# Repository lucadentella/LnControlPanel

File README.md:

# LnControlPanel

## Description

LnControlPanel is an opensource board to create Loconet control panels.

## What's new :tada:

- 23/04/2022, new board version, with MCP23017 chips instead of CJMCU modules
- 05/03/2022, new firmware (2.0) with support for new Adafruit libraries

## Features :trophy:

 - **32** independent channels:
   - each channel can be configured as **input** (to *control*) or as **output** (to *monitor)*
   - each channel can control/monitor a **turnout** or a **sensor**
   - each channel can have its own **address**
 - Two Loconet connectors for **cascade** connection
 - Based on **Arduino** framework and opensource libraries
 - Configurable using a simple **menu** via **serial** connection

## Tutorials :video_camera:
 - [LnControlPanel on Youtube (ENG)](https://youtu.be/r6l4IHOCdZg)
 - [LnControlPanel su Youtube (ITA)](https://youtu.be/eZ9PHgq4dks)

## Resources :open_file_folder:
 - [Eagle files - board with CJMCU modules](https://github.com/lucadentella/LnControlPanel/tree/main/Eagle/Modules) (schematic / PCB)
 - [Eagle files - board with MCP23017 chips](https://github.com/lucadentella/LnControlPanel/tree/main/Eagle/Chips) (schematic / PCB) 
 - [Arduino firmware](https://github.com/lucadentella/LnControlPanel/tree/main/Arduino)

## Documentation :notebook:
 - [Schematic - board with CJMCU modules](https://github.com/lucadentella/LnControlPanel/tree/main/Documentation/Schematics-modules.pdf) (PDF)
 - [Schematic - board with MCP23017 chips](https://github.com/lucadentella/LnControlPanel/tree/main/Documentation/Schematics-chips.pdf) (PDF)
 - [Part list](https://github.com/lucadentella/LnControlPanel/tree/main/Documentation/PARTLIST.md)
 - [How to configure the channels](https://github.com/lucadentella/LnControlPanel/tree/main/Documentation/CONFIGURATION.md)
 - [How to connect buttons/LEDs](https://github.com/lucadentella/LnControlPanel/tree/main/Documentation/CONNECTIONS.md) 

## Requirements :heavy_check_mark:
 - [mrrwa Loconet Library](https://github.com/mrrwa/LocoNet)
 - [Adafruit MCP23017 Library](https://github.com/adafruit/Adafruit-MCP23017-Arduino-Library)

*The libraries above can be installed via the* [Library Manager](https://www.arduino.cc/en/guide/libraries)

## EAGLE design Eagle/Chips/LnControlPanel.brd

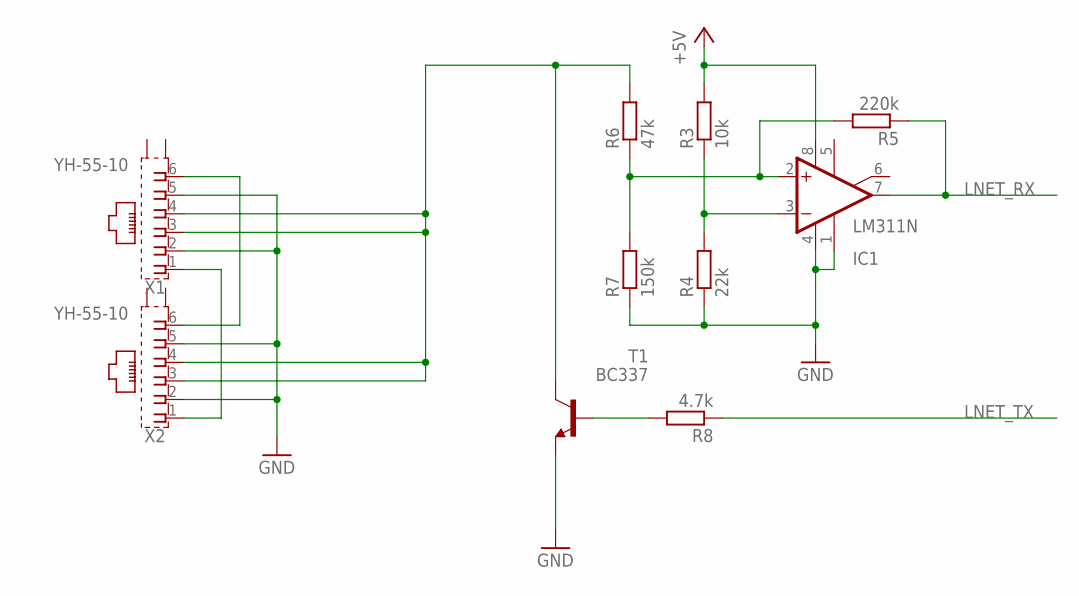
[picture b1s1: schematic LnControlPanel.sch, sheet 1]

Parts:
IC1: LM311N; DIL08
R3: 10k; 0207/2V
R4: 22k; 0207/2V
R5: 220k; 0207/2V
R6: 47k; 0207/2V
R7: 150k; 0207/2V
R8: 4.7k; 0207/2V
T1: BC337; TO92
X1, X2: YH-55-10

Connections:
+5V: IC1.8 (V+), R3.2; also elsewhere on the board
GND: IC1.1 (GND), IC1.4 (V-), R4.1, R7.1, T1.1 (E), X1.2, X1.5, X2.2, X2.5; also elsewhere on the board
LNET: R6.2, T1.3 (C), X1.3, X1.4, X2.3, X2.4
LNET_RX: IC1.7 (OUT), R5.1; also elsewhere on the board
LNET_TX: R8.1; also elsewhere on the board
unnamed: R8.2, T1.2 (B)
unnamed: IC1.3 (-IN), R3.1, R4.2
unnamed: IC1.2 (+IN), R5.2, R6.1, R7.2
unnamed: X1.1, X2.1
unnamed: X1.6, X2.6

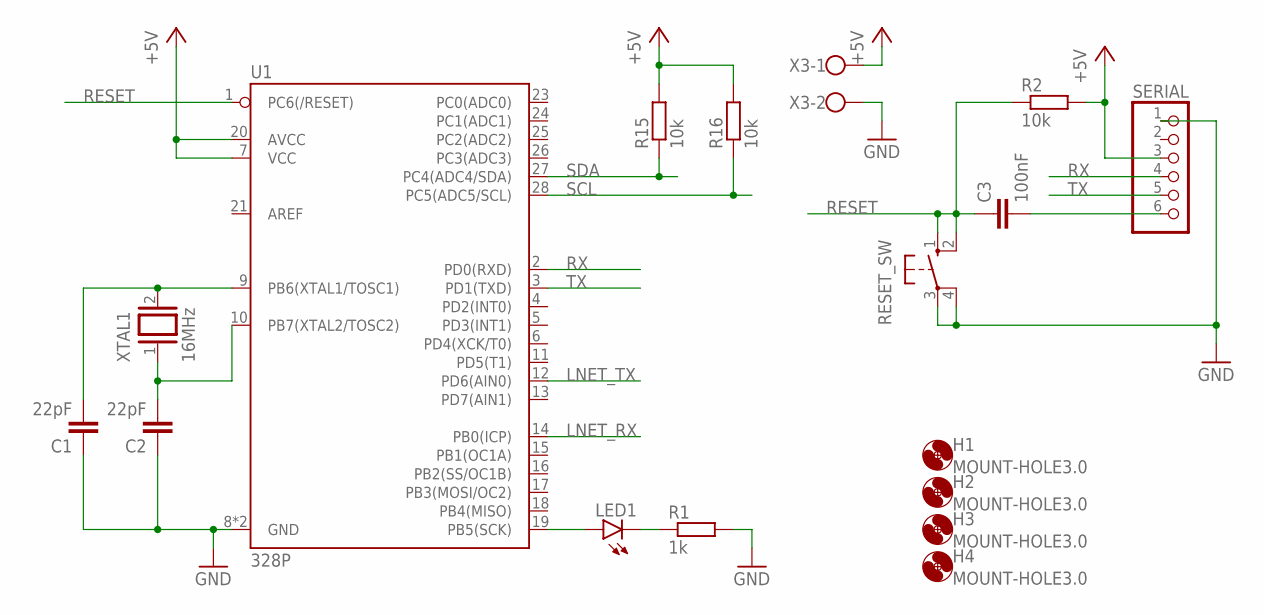
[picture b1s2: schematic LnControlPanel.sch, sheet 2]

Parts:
C1, C2: 22pF; C025-025X050
C3: 100nF; C050-030X075
H1, H2, H3, H4: MOUNT-HOLE3.0; 3,0
LED1: LED3MM
R1: 1k; 0207/2V
R2, R15, R16: 10k; 0207/2V
RESET_SW: 10-XX; B3F-10XX
SERIAL: PINHD-1X6; 1X06
U1: 328P; DIP28
X3: W237-102
XTAL1: 16MHz; QS

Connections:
+5V: R2.2, R15.2, R16.2, SERIAL.3, U1.7 (VCC), U1.20 (AVCC), X3.1; also elsewhere on the board
GND: C1.1, C2.1, R1.2, RESET_SW.3, RESET_SW.4 (P1), SERIAL.1, U1.8 (GND), U1.22 (GND), X3.2; also elsewhere on the board
LNET_RX: U1.14 (PB0(ICP)); also elsewhere on the board
LNET_TX: U1.12 (PD6(AIN0)); also elsewhere on the board
unnamed: C2.2, U1.10 (PB7(XTAL2/TOSC2)), XTAL1.1
unnamed: C1.2, U1.9 (PB6(XTAL1/TOSC1)), XTAL1.2
unnamed: C3.2, SERIAL.6
unnamed: LED1.A, U1.19 (PB5(SCK))
unnamed: LED1.K (C), R1.1
RESET: C3.1, R2.1, RESET_SW.1 (S), RESET_SW.2 (S1), U1.1 (PC6(/RESET))
RX: SERIAL.4, U1.2 (PD0(RXD))
SCL: R16.1, U1.28 (PC5(ADC5/SCL)); also elsewhere on the board
SDA: R15.1, U1.27 (PC4(ADC4/SDA)); also elsewhere on the board
TX: SERIAL.5, U1.3 (PD1(TXD))

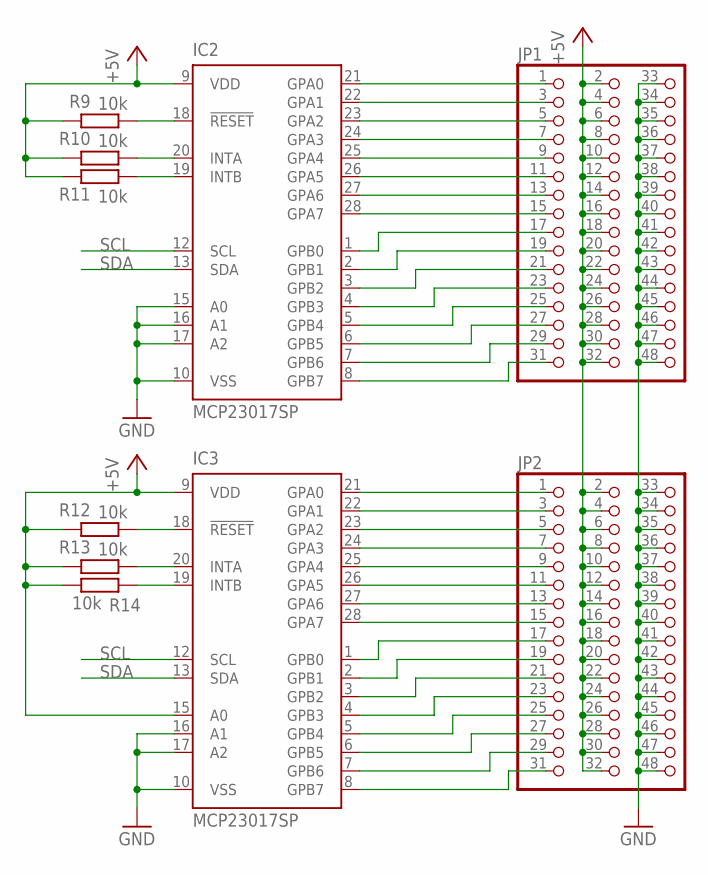
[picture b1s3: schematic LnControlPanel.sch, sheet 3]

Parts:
IC2, IC3: MCP23017SP; DIL28-3
JP1, JP2: PINHD-3X16; 3X16
R9, R10, R11, R12, R13, R14: 10k; 0207/2V

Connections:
+5V: IC2.9 (VDD), IC3.9 (VDD), IC3.15 (A0), JP1.2, JP1.4, JP1.6, JP1.8, JP1.10, JP1.12, JP1.14, JP1.16, JP1.18, JP1.20, JP1.22, JP1.24, JP1.26, JP1.28, JP1.30, JP1.32, JP2.2, JP2.4, JP2.6, JP2.8, JP2.10, JP2.12, JP2.14, JP2.16, JP2.18, JP2.20, JP2.22, JP2.24, JP2.26, JP2.28, JP2.30, JP2.32, R9.2, R10.2, R11.2, R12.2, R13.2, R14.1; also elsewhere on the board
GND: IC2.10 (VSS), IC2.15 (A0), IC2.16 (A1), IC2.17 (A2), IC3.10 (VSS), IC3.16 (A1), IC3.17 (A2), JP1.33, JP1.34, JP1.35, JP1.36, JP1.37, JP1.38, JP1.39, JP1.40, JP1.41, JP1.42, JP1.43, JP1.44, JP1.45, JP1.46, JP1.47, JP1.48, JP2.33, JP2.34, JP2.35, JP2.36, JP2.37, JP2.38, JP2.39, JP2.40, JP2.41, JP2.42, JP2.43, JP2.44, JP2.45, JP2.46, JP2.47, JP2.48; also elsewhere on the board
unnamed: IC2.21 (GPA0), JP1.1
unnamed: IC2.22 (GPA1), JP1.3
unnamed: IC2.23 (GPA2), JP1.5
unnamed: IC2.24 (GPA3), JP1.7
unnamed: IC2.25 (GPA4), JP1.9
unnamed: IC2.26 (GPA5), JP1.11
unnamed: IC2.27 (GPA6), JP1.13
unnamed: IC2.28 (GPA7), JP1.15
unnamed: IC2.1 (GPB0), JP1.17
unnamed: IC2.2 (GPB1), JP1.19
unnamed: IC2.3 (GPB2), JP1.21
unnamed: IC2.4 (GPB3), JP1.23
unnamed: IC2.5 (GPB4), JP1.25
unnamed: IC2.6 (GPB5), JP1.27
unnamed: IC2.7 (GPB6), JP1.29
unnamed: IC2.8 (GPB7), JP1.31
unnamed: IC3.21 (GPA0), JP2.1
unnamed: IC3.22 (GPA1), JP2.3
unnamed: IC3.23 (GPA2), JP2.5
unnamed: IC3.24 (GPA3), JP2.7
unnamed: IC3.25 (GPA4), JP2.9
unnamed: IC3.26 (GPA5), JP2.11
unnamed: IC3.27 (GPA6), JP2.13
unnamed: IC3.28 (GPA7), JP2.15
unnamed: IC3.1 (GPB0), JP2.17
unnamed: IC3.2 (GPB1), JP2.19
unnamed: IC3.3 (GPB2), JP2.21
unnamed: IC3.4 (GPB3), JP2.23
unnamed: IC3.5 (GPB4), JP2.25
unnamed: IC3.6 (GPB5), JP2.27
unnamed: IC3.7 (GPB6), JP2.29
unnamed: IC3.8 (GPB7), JP2.31
unnamed: IC3.18 (!RESET), R12.1
unnamed: IC2.18 (!RESET), R9.1
unnamed: IC2.20 (INTA), R10.1
unnamed: IC2.19 (INTB), R11.1
unnamed: IC3.20 (INTA), R13.1
unnamed: IC3.19 (INTB), R14.2
SCL: IC2.12 (SCL), IC3.12 (SCL); also elsewhere on the board
SDA: IC2.13 (SDA), IC3.13 (SDA); also elsewhere on the board

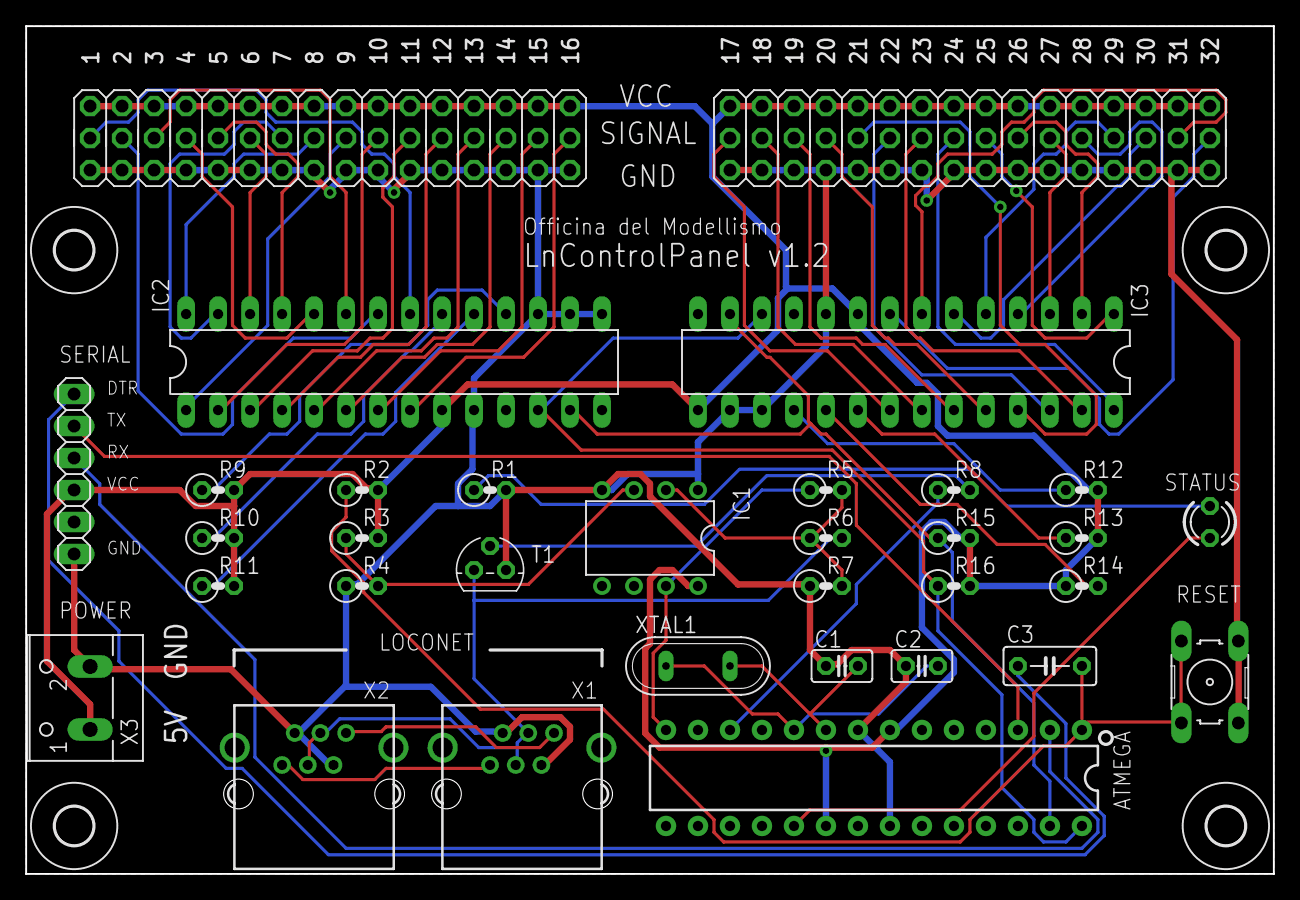
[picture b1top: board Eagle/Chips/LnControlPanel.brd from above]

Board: 2 copper layers, 99.1 x 67.3 mm, 37 parts (0 on the bottom side), 58 nets.

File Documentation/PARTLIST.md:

# Part list :gift:
| ID | Description | 
|--|--|
| R1 | 1Kohm 1/4W resistor |
| R2,3 | 10Kohm 1/4W resistor |
| R4 | 22Kohm 1/4W resistor |
| R5 | 220Kohm 1/4W resistor |
| R6 | 47Kohm 1/4W resistor |
| R7 | 150Kohm 1/4W resistor |
| R8 | 4.7Kohm 1/4W resistor |
| C1,C2 | 22pF ceramic capacitor |
| C3 | 100nF ceramic capacitor |
| XTAL1 | 16MHz crystal oscillator |
| T1 | BC337 NPN transistor |
| LED1 | 3mm LED |
| IC1 | LM311N |
| U1 | ATmega328p |
| M1,M2 | CJMCU-2317 module |
| RESET_SW | Tactile pushbutton |
| X1,X2 | RJ11 PCB connector |
| X3 | 2P terminal block |
| JP1,JP2 | 3x16 pin header |
| JP3 | 1x6 pin header |

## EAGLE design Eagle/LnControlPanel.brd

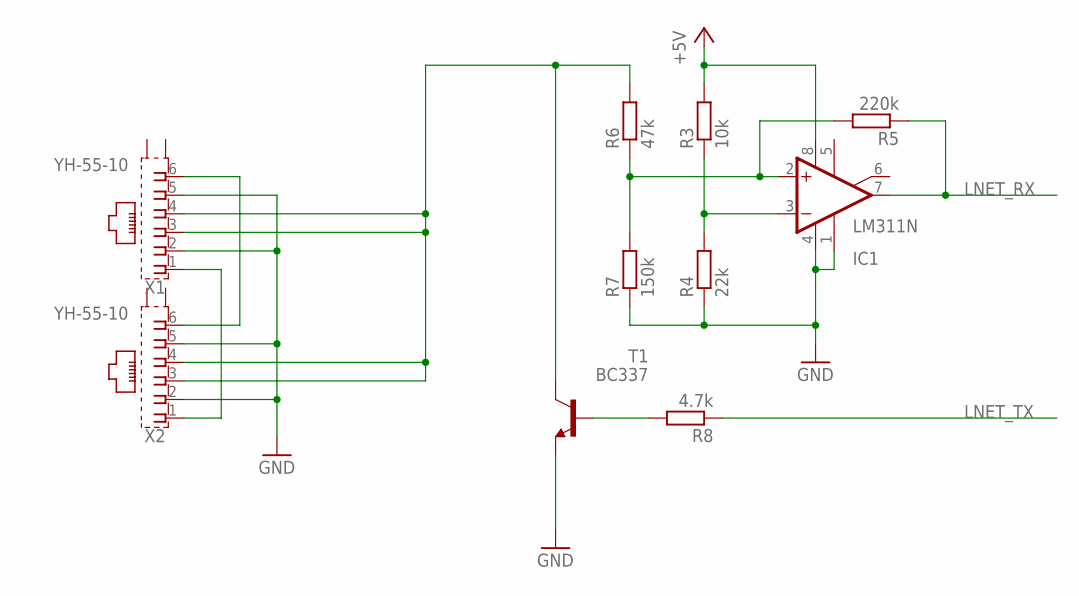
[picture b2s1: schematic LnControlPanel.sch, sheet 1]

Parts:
IC1: LM311N; DIL08
R3: 10k; 0207/2V
R4: 22k; 0207/2V
R5: 220k; 0207/2V
R6: 47k; 0207/2V
R7: 150k; 0207/2V
R8: 4.7k; 0207/2V
T1: BC337; TO92
X1, X2: YH-55-10

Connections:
+5V: IC1.8 (V+), R3.2; also elsewhere on the board
GND: IC1.1 (GND), IC1.4 (V-), R4.1, R7.1, T1.1 (E), X1.2, X1.5, X2.2, X2.5; also elsewhere on the board
LNET: R6.2, T1.3 (C), X1.3, X1.4, X2.3, X2.4
LNET_RX: IC1.7 (OUT), R5.1; also elsewhere on the board
LNET_TX: R8.1; also elsewhere on the board
unnamed: R8.2, T1.2 (B)
unnamed: IC1.3 (-IN), R3.1, R4.2
unnamed: IC1.2 (+IN), R5.2, R6.1, R7.2
unnamed: X1.1, X2.1
unnamed: X1.6, X2.6

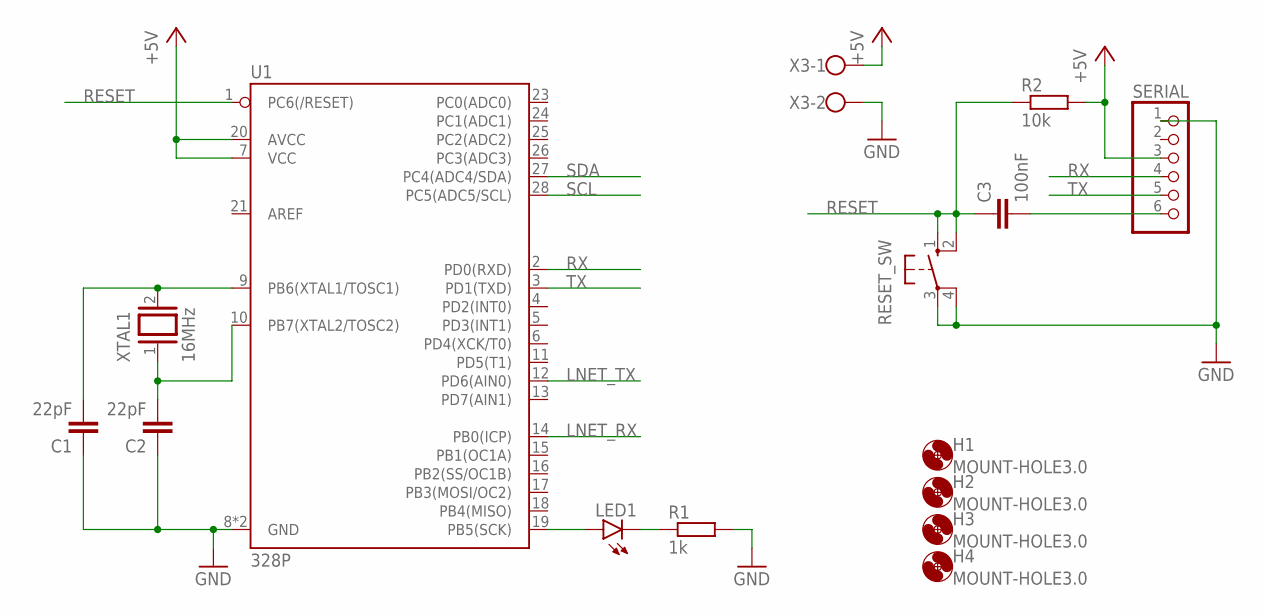
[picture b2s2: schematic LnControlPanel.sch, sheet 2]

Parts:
C1, C2: 22pF; C025-025X050
C3: 100nF; C050-030X075
H1, H2, H3, H4: MOUNT-HOLE3.0; 3,0
LED1: LED3MM
R1: 1k; 0207/2V
R2: 10k; 0207/2V
RESET_SW: 10-XX; B3F-10XX
SERIAL: PINHD-1X6; 1X06
U1: 328P; DIP28
X3: W237-102
XTAL1: 16MHz; QS

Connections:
+5V: R2.2, SERIAL.3, U1.7 (VCC), U1.20 (AVCC), X3.1; also elsewhere on the board
GND: C1.1, C2.1, R1.2, RESET_SW.3, RESET_SW.4 (P1), SERIAL.1, U1.8 (GND), U1.22 (GND), X3.2; also elsewhere on the board
LNET_RX: U1.14 (PB0(ICP)); also elsewhere on the board
LNET_TX: U1.12 (PD6(AIN0)); also elsewhere on the board
unnamed: C2.2, U1.10 (PB7(XTAL2/TOSC2)), XTAL1.1
unnamed: C1.2, U1.9 (PB6(XTAL1/TOSC1)), XTAL1.2
unnamed: C3.2, SERIAL.6
unnamed: LED1.A, U1.19 (PB5(SCK))
unnamed: LED1.K (C), R1.1
RESET: C3.1, R2.1, RESET_SW.1 (S), RESET_SW.2 (S1), U1.1 (PC6(/RESET))
RX: SERIAL.4, U1.2 (PD0(RXD))
SCL: U1.28 (PC5(ADC5/SCL)); also elsewhere on the board
SDA: U1.27 (PC4(ADC4/SDA)); also elsewhere on the board
TX: SERIAL.5, U1.3 (PD1(TXD))

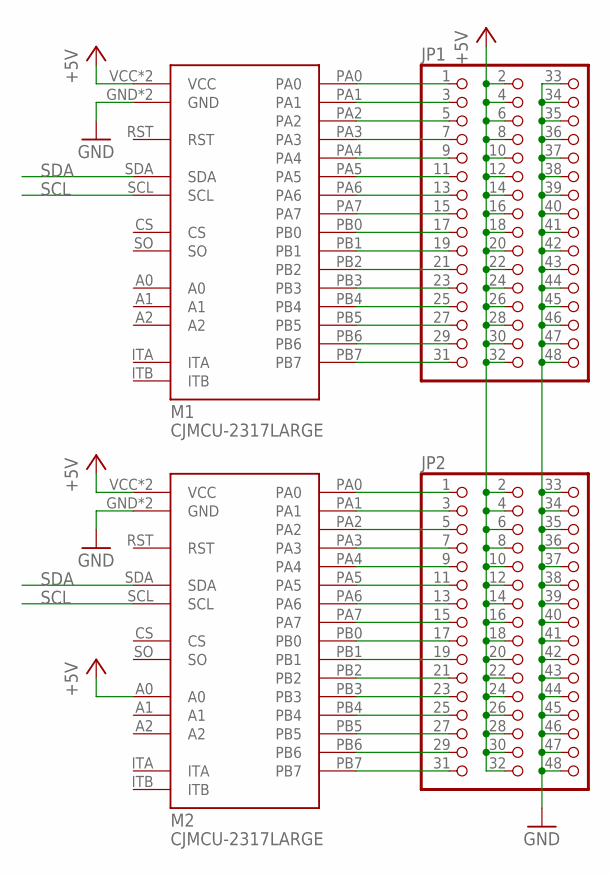
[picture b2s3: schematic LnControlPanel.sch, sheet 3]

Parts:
JP1, JP2: PINHD-3X16; 3X16
M1, M2: CJMCU-2317LARGE; CJMCU-2317-PACKAGE2

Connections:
+5V: JP1.2, JP1.4, JP1.6, JP1.8, JP1.10, JP1.12, JP1.14, JP1.16, JP1.18, JP1.20, JP1.22, JP1.24, JP1.26, JP1.28, JP1.30, JP1.32, JP2.2, JP2.4, JP2.6, JP2.8, JP2.10, JP2.12, JP2.14, JP2.16, JP2.18, JP2.20, JP2.22, JP2.24, JP2.26, JP2.28, JP2.30, JP2.32, M1.VCC, M1.VCC_2 (VCC), M2.A0, M2.VCC, M2.VCC_2 (VCC); also elsewhere on the board
GND: JP1.33, JP1.34, JP1.35, JP1.36, JP1.37, JP1.38, JP1.39, JP1.40, JP1.41, JP1.42, JP1.43, JP1.44, JP1.45, JP1.46, JP1.47, JP1.48, JP2.33, JP2.34, JP2.35, JP2.36, JP2.37, JP2.38, JP2.39, JP2.40, JP2.41, JP2.42, JP2.43, JP2.44, JP2.45, JP2.46, JP2.47, JP2.48, M1.GND, M1.GND_2 (GND), M2.GND, M2.GND_2 (GND); also elsewhere on the board
unnamed: JP1.1, M1.PA0
unnamed: JP1.3, M1.PA1
unnamed: JP1.5, M1.PA2
unnamed: JP1.7, M1.PA3
unnamed: JP1.9, M1.PA4
unnamed: JP1.11, M1.PA5
unnamed: JP1.13, M1.PA6
unnamed: JP1.15, M1.PA7
unnamed: JP1.17, M1.PB0
unnamed: JP1.19, M1.PB1
unnamed: JP1.21, M1.PB2
unnamed: JP1.23, M1.PB3
unnamed: JP1.25, M1.PB4
unnamed: JP1.27, M1.PB5
unnamed: JP1.29, M1.PB6
unnamed: JP1.31, M1.PB7
unnamed: JP2.1, M2.PA0
unnamed: JP2.3, M2.PA1
unnamed: JP2.5, M2.PA2
unnamed: JP2.7, M2.PA3
unnamed: JP2.9, M2.PA4
unnamed: JP2.11, M2.PA5
unnamed: JP2.13, M2.PA6
unnamed: JP2.15, M2.PA7
unnamed: JP2.17, M2.PB0
unnamed: JP2.19, M2.PB1
unnamed: JP2.21, M2.PB2
unnamed: JP2.23, M2.PB3
unnamed: JP2.25, M2.PB4
unnamed: JP2.27, M2.PB5
unnamed: JP2.29, M2.PB6
unnamed: JP2.31, M2.PB7
SCL: M1.SCL, M2.SCL; also elsewhere on the board
SDA: M1.SDA, M2.SDA; also elsewhere on the board

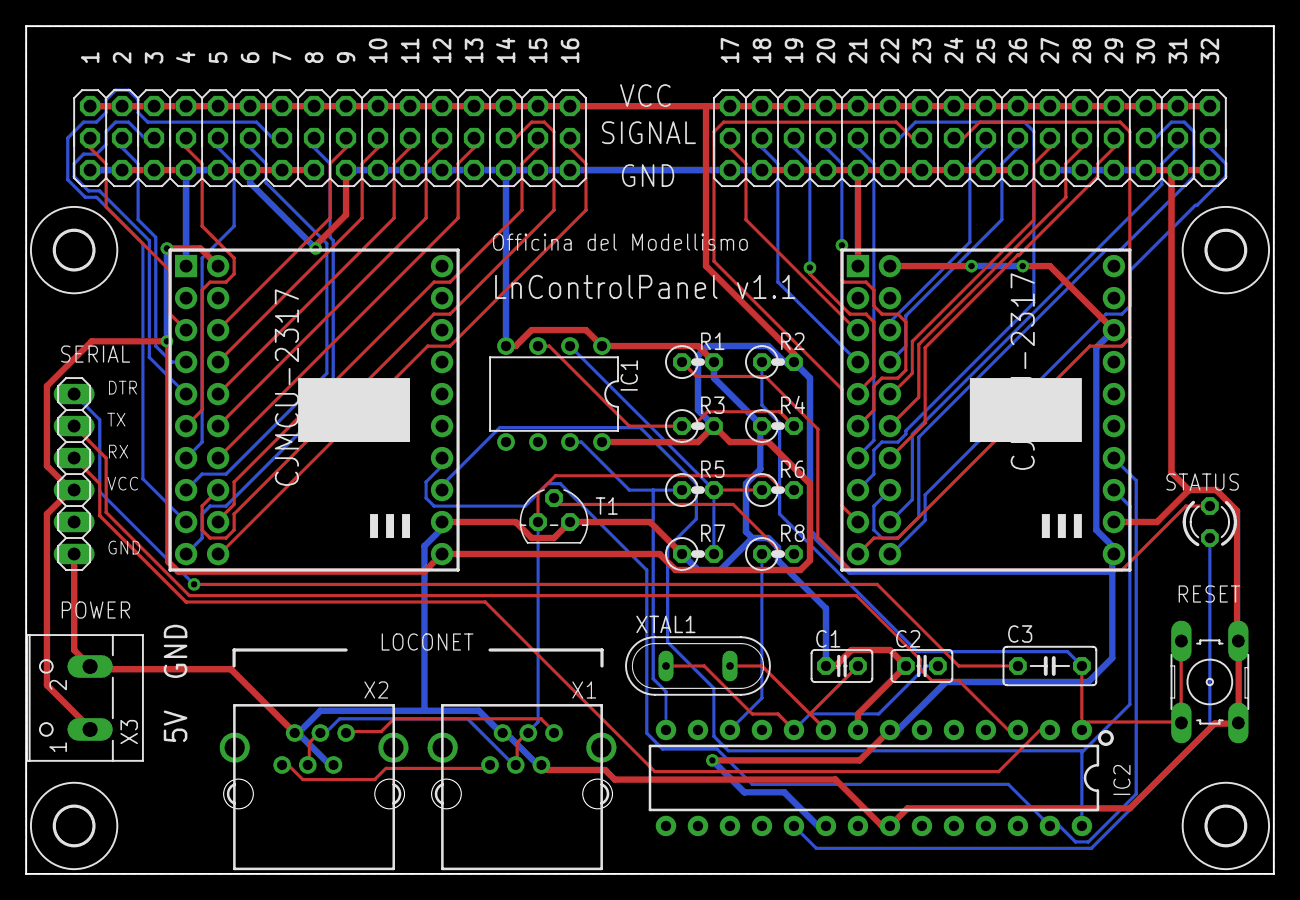
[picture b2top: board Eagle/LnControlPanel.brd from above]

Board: 2 copper layers, 99.1 x 67.3 mm, 29 parts (0 on the bottom side), 52 nets.

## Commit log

2021-05-02 Image added
2021-05-02 License added
2021-05-02 Features added
2021-05-02 Partlist added
2021-05-11 Connection images added
2021-05-11 License badge added
2021-05-11 Documentation moved to a dedicated folder
2021-05-11 New images for the Configuration page
2021-05-11 Image links fixed
2021-05-12 Fix link
2021-05-14 Arduino and Eagle files added
2021-05-14 Schematic in PDF added
2021-05-14 Links to YT tutorials added
2021-09-03 Updated Loconet switch command for more compatibility
2022-02-28 Update LnControlPanel.ino
    Hello,
    please check my proposed changes:
    I registered that the newer Adafruit-Librariy does not work correctly with the sketch. The change of the Adress-Definition in Line 61 and 62 is to ensure the compatibility with the recent Adafruit-Li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
    Then i registered in my build that the inputs of the second MCP have no function. In cause of the Division by 2 in Line 151 the Inputs of the second MCP are not registered. After deleting the term "/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
    Luca, i have to thank you for this project. This is exactly what I needed, THANK YOU!
    Greetings from Germay,
2022-03-05 Adafruit MCP library updated and bugfixing
2022-04-23 New board version added, with MCP23017 chips instead of CJMCU modules

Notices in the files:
README.md:
License: CC-BY-NC-SA
parts and their libraries:
SparkFun-IC-Microcontroller: Licensing: Creative Commons ShareAlike 4.0 International - https://creativecommons.org/licenses/by-sa/4.0
